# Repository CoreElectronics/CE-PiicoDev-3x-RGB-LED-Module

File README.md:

# PiicoDev® 3x RGB LED Module Hardware Repo

This is the repo for the Core Electronics [PiicoDev 3x RGB LED Module](https://core-electronics.com.au/catalog/product/view/sku/CE07910).

## License
This project is open source - please review the LICENSE.md file for further licensing information.

If you have any technical questions, or concerns about licensing, please contact technical support on the [Core Electronics forums](https://forum.core-electronics.com.au/).

*\"PiicoDev\" and the PiicoDev logo are trademarks of Core Electronics Pty Ltd.*

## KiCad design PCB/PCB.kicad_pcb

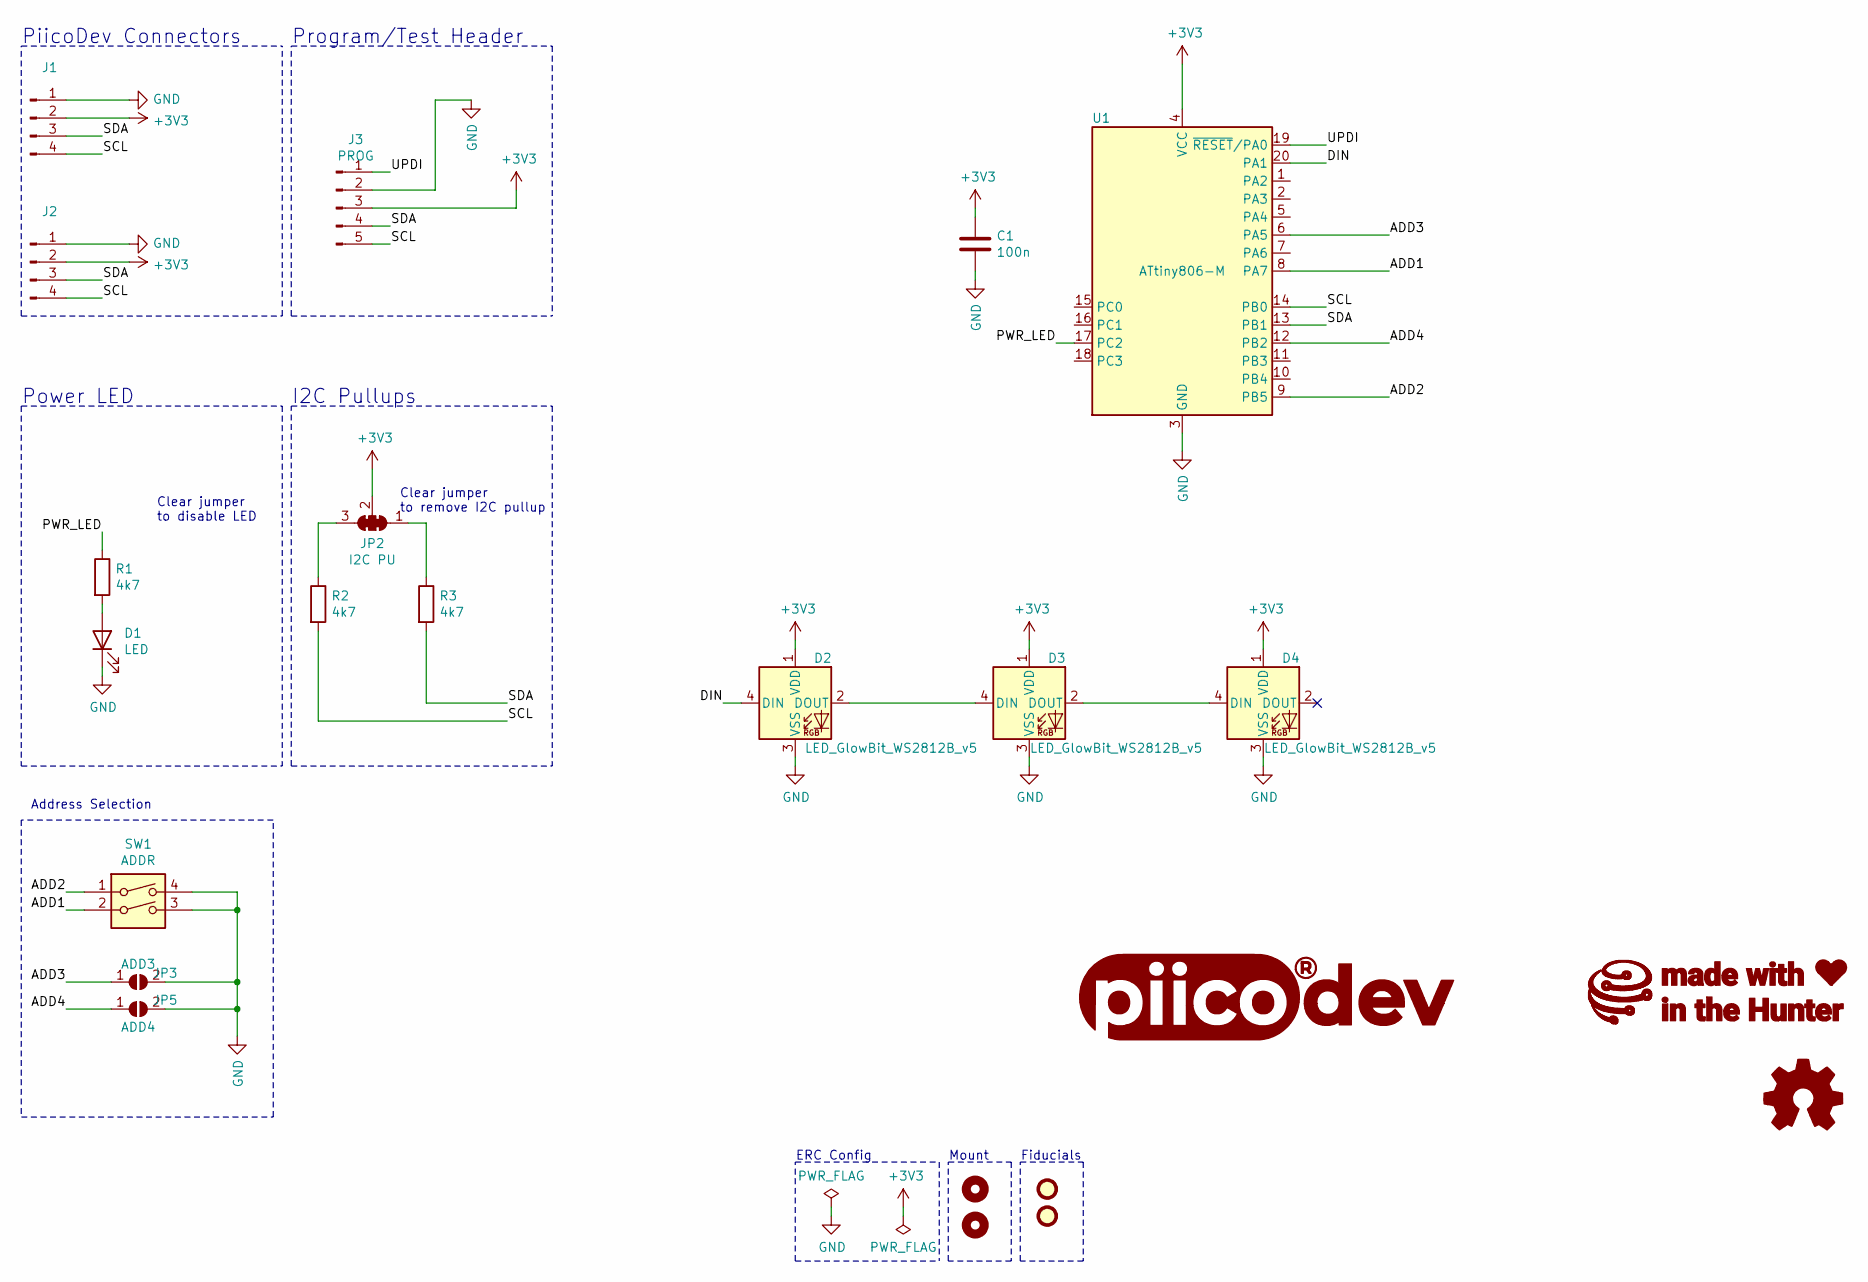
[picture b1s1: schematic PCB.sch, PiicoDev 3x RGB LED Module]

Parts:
C1: 100n; C_0402_1005Metric
D1: LED; LED_0603_1608Metric
D2, D3, D4: LED_GlowBit_WS2812B_v5; LED_GlowBit_WS2812B_NoSilk
FID1, FID2: Fiducial; Fiducial_1mm_Mask2mm
G1: LOGO_PiicoDev; piicodev_logo_14.2x3.4mm
G2: LOGO_CoreElectronics_no-text; CoreElectronics_logo_5mm
G3: LOGO_made-with-love; piicodev_logo_14.2x3.4mm
H1, H2: MountingHole; MountingHole_2.7mm_M2.5_PadClearance_1.2
J1, J2: JST_SH_SM04B-SRSS-TB_1x04-1MP_P1.00mm_Horizontal
J3: PROG; PiicoDev_header_programming_test_1x05_P1.27mm_Vertical
JP2: I2C PU; SolderJumper-3_P1.3mm_Closed_RoundedPad1.0x1.5mm_NumberLabe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
JP3: ADD3; SolderJumper-2_P1.3mm_Open_RoundedPad1.0x1.5mm
JP5: ADD4; SolderJumper-2_P1.3mm_Open_RoundedPad1.0x1.5mm
LOGO1: Logo_Open_Hardware_Small; oshw
R1, R2, R3: 4k7; R_0402_1005Metric
SW1: ADDR; SW_DIP_SPSTx02_Slide_DSHP
U1: ATtiny806-M; VQFN-20-1EP_3x3mm_P0.4mm_EP1.7x1.7mm

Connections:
+3V3: C1.1, D2.1 (VDD), D3.1 (VDD), D4.1 (VDD), J1.2, J2.2, J3.3, JP2.2 (C), U1.4 (VCC)
/ADD1: SW1.2, U1.8 (PA7)
/ADD2: SW1.1, U1.9 (PB5)
/ADD3: JP3.1 (A), U1.6 (PA5)
/ADD4: JP5.1 (A), U1.12 (PB2)
/DIN: D2.4 (DIN), U1.20 (PA1)
/PWR_LED: R1.1, U1.17 (PC2)
/SCL: J1.4, J2.4, J3.5, R2.2, U1.14 (PB0)
/SDA: J1.3, J2.3, J3.4, R3.2, U1.13 (PB1)
/UPDI: J3.1, U1.19 (~RESET~/PA0)
GND: C1.2, D1.1 (K), D2.3 (VSS), D3.3 (VSS), D4.3 (VSS), J1.1, J2.1, J3.2, JP3.2 (B), JP5.2 (B), SW1.3, SW1.4, U1.3 (GND), U1.21 (GND)
unnamed: D1.2 (A), R1.2
unnamed: D2.2 (DOUT), D3.4 (DIN)
unnamed: D3.2 (DOUT), D4.4 (DIN)
unnamed: JP2.1 (A), R3.1
unnamed: JP2.3 (B), R2.1

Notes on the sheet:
ERC Config
Fiducials
Mount
PiicoDev Connectors
Program/Test Header
Clear jumper to remove I2C pullup
I2C Pullups
Power LED
Clear jumper to disable LED
Address Selection

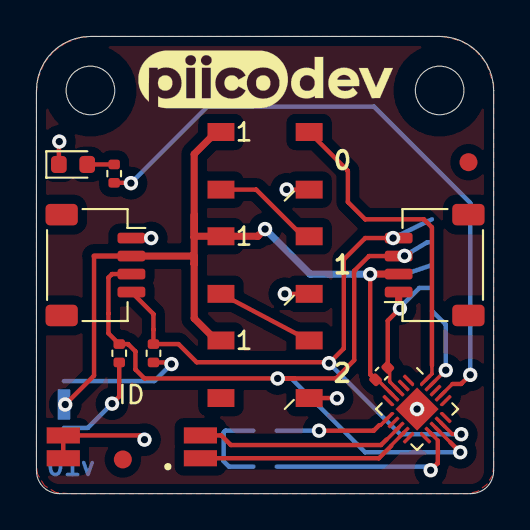
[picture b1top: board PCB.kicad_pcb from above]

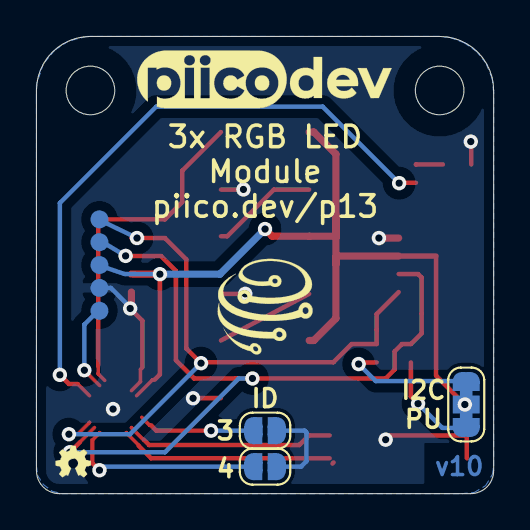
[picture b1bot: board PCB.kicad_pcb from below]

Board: 2 copper layers, 25.4 x 25.4 mm, 24 parts (7 on the bottom side), 16 nets.

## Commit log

2021-08-26 Make pwr LED user controllable
2021-10-08 rotate ID switch
2022-03-21 update resistors to 10k, add schematic
2022-03-21 update title block
